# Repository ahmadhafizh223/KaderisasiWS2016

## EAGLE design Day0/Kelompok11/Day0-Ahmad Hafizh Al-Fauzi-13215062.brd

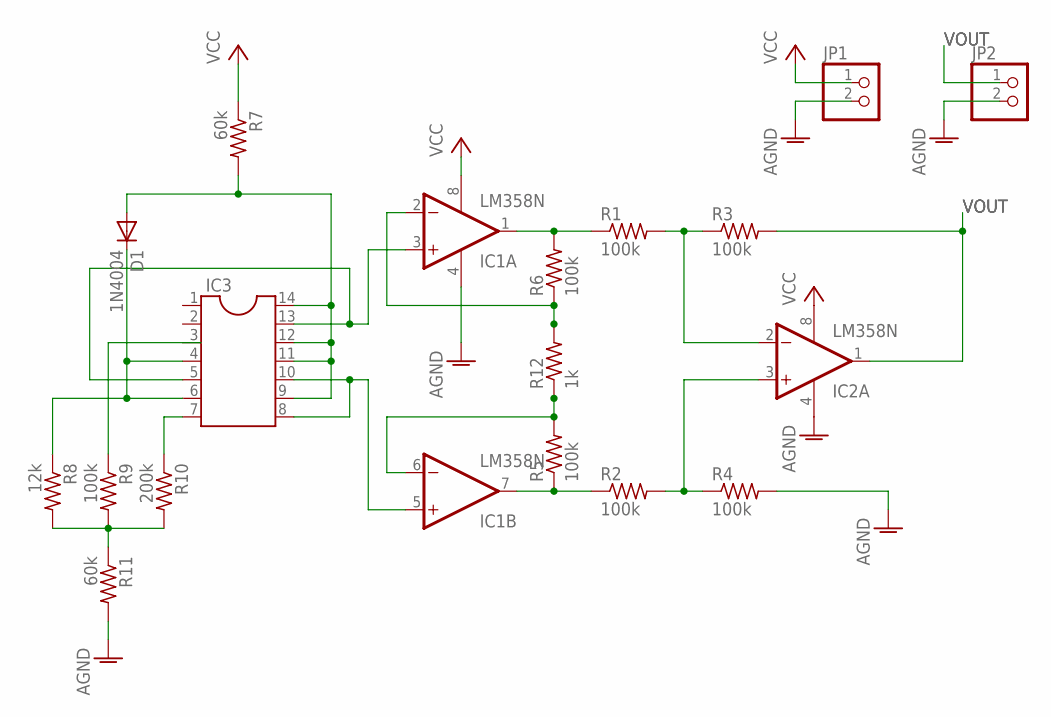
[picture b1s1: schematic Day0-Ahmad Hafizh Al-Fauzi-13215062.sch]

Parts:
D1: 1N4004; DO41-10
IC1, IC2: LM358N; DIL08
IC3: DIL14
JP1, JP2: PINHD-1X2; 1X02
R1, R2, R3, R4, R5, R6, R9: 100k; 0204/7
R7, R11: 60k; 0204/7
R8: 12k; 0204/7
R10: 200k; 0204/7
R12: 1k; 0204/7

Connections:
AGND: IC1.4 (V-), IC2.4 (V-), JP1.2, JP2.2, R4.2, R11.2
MALE_HEADER1: JP1.1
unnamed: R8.2, R9.2, R10.2, R11.1
unnamed: IC1.6 (-IN), R5.2, R12.1
unnamed: IC1.2 (-IN), R6.1, R12.2
unnamed: D1.A, IC3.9, IC3.11, IC3.12, IC3.14, R7.2
unnamed: IC1.3 (+IN), IC3.5, IC3.13
unnamed: D1.C, IC3.4, IC3.6, R8.1
unnamed: IC3.3, R9.1
unnamed: IC1.5 (+IN), IC3.8, IC3.10
unnamed: IC2.3 (+IN), R2.2, R4.1
unnamed: IC1.7 (OUT), R2.1, R5.1
unnamed: IC1.1 (OUT), R1.1, R6.2
unnamed: IC2.2 (-IN), R1.2, R3.1
unnamed: IC3.7, R10.1
VCC: IC1.8 (V+), IC2.8 (V+), R7.1
VOUT: IC2.1 (OUT), JP2.1, R3.2

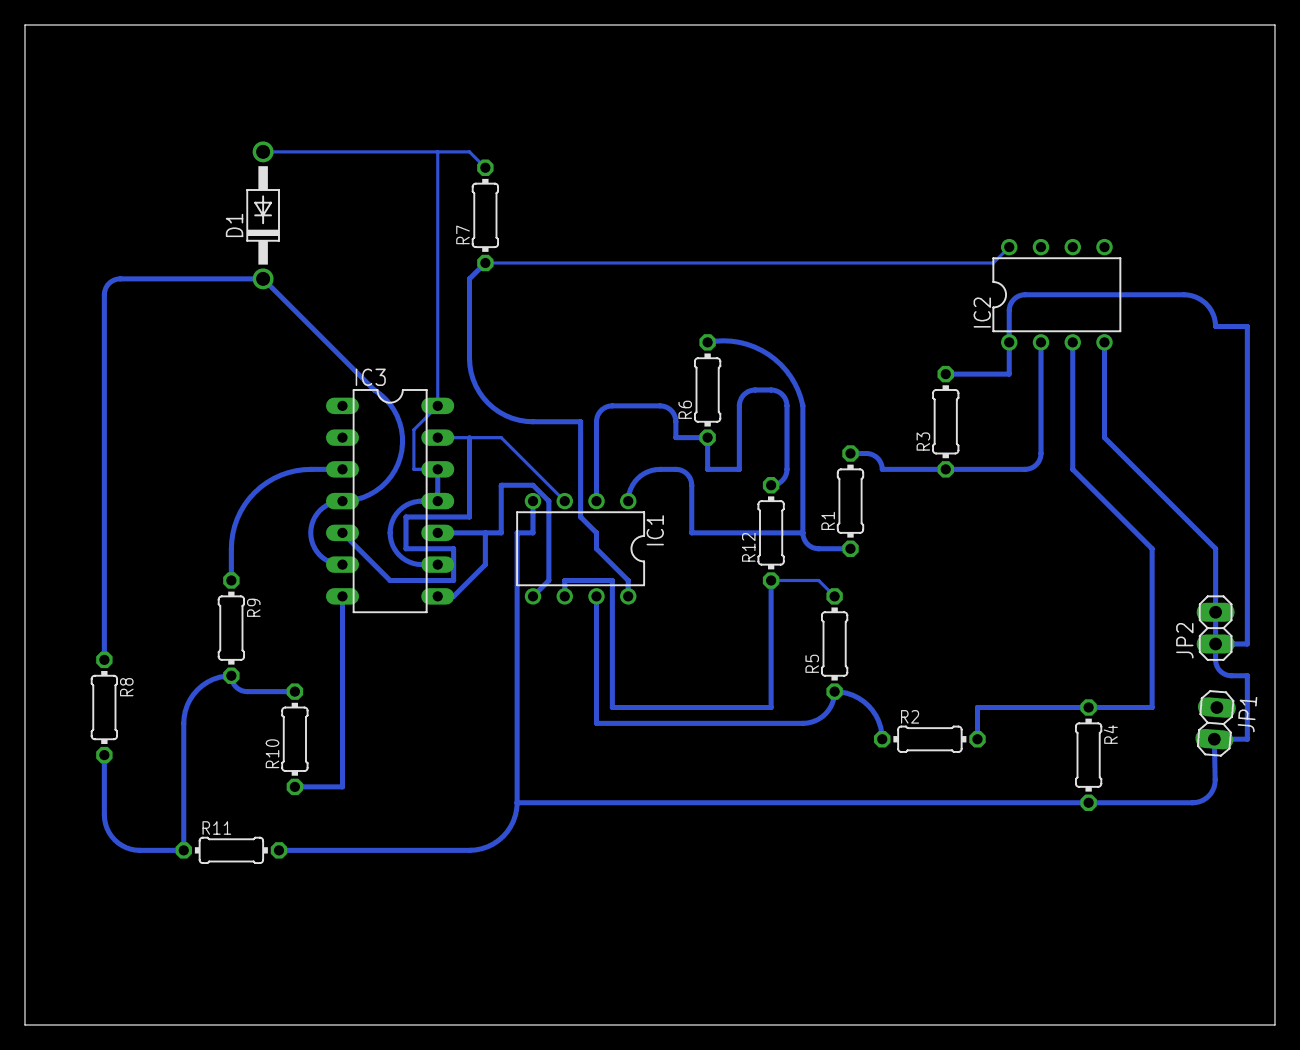
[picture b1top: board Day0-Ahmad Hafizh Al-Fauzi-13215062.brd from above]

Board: 2 copper layers, 100.0 x 80.0 mm, 18 parts (0 on the bottom side), 16 nets.

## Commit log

2016-09-22 Create Kelompok 11
